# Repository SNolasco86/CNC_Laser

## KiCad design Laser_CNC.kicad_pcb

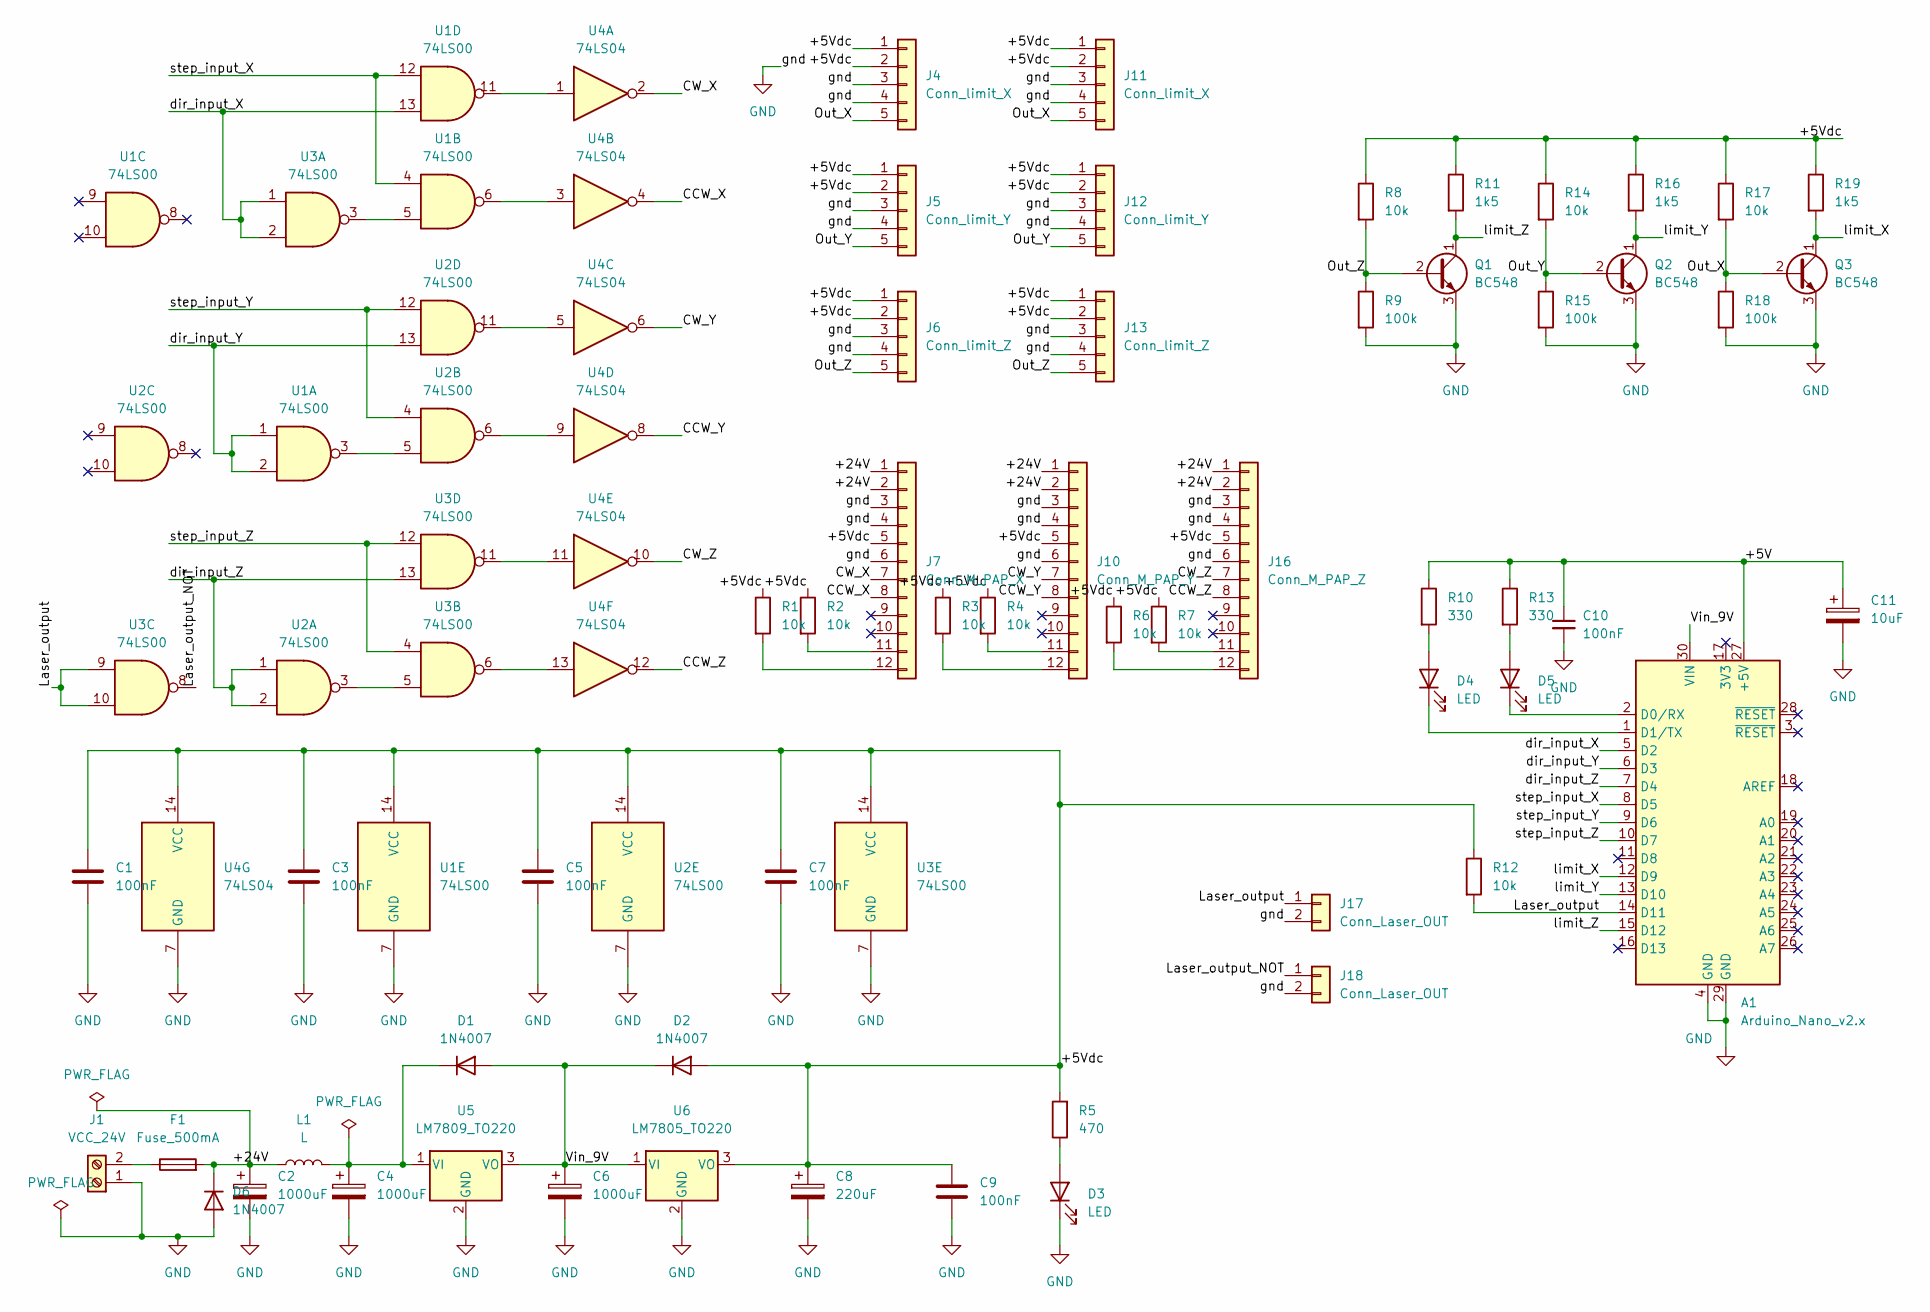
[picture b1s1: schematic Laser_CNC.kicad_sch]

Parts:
A1: Arduino_Nano_v2.x; Arduino_Nano
C1, C3, C5, C7, C9, C10: 100nF; C_Disc_D4.7mm_W2.5mm_P5.00mm
C2: 1000uF; CP_Radial_D13.0mm_P7.50mm
C4, C6: 1000uF; CP_Radial_D13.0mm_P5.00mm
C8: 220uF; CP_Radial_D10.0mm_P3.50mm
C11: 10uF; CP_Radial_D10.0mm_P3.50mm
D1, D2, D6: 1N4007; D_DO-41_SOD81_P10.16mm_Horizontal
D3, D4, D5: LED; LED_D5.0mm
F1: Fuse_500mA; Fuseholder_Cylinder-5x20mm_Stelvio-Kontek_PTF78_Horizontal_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
J1: VCC_24V; TerminalBlock_bornier-2_P5.08mm
J4, J11: Conn_limit_X; Molex_SL_171971-0005_1x05_P2.54mm_Vertical
J5, J12: Conn_limit_Y; Molex_SL_171971-0005_1x05_P2.54mm_Vertical
J6, J13: Conn_limit_Z; Molex_SL_171971-0005_1x05_P2.54mm_Vertical
J7: Conn_M_PAP_X; Molex_SL_171971-0012_1x12_P2.54mm_Vertical
J10: Conn_M_PAP_Y; Molex_SL_171971-0012_1x12_P2.54mm_Vertical
J16: Conn_M_PAP_Z; Molex_SL_171971-0012_1x12_P2.54mm_Vertical
J17, J18: Conn_Laser_OUT; JST_EH_B2B-EH-A_1x02_P2.50mm_Vertical
L1: L; L_Radial_D6.0mm_P4.00mm
Q1, Q2, Q3: BC548; TO-92_Inline
R1, R2, R3, R4, R6, R7, R8, R12, R14, R17: 10k; R_Axial_DIN0207_L6.3mm_D2.5mm_P10.16mm_Horizontal
R5: 470; R_Axial_DIN0207_L6.3mm_D2.5mm_P10.16mm_Horizontal
R9, R15, R18: 100k; R_Axial_DIN0207_L6.3mm_D2.5mm_P10.16mm_Horizontal
R10, R13: 330; R_Axial_DIN0207_L6.3mm_D2.5mm_P10.16mm_Horizontal
R11, R16, R19: 1k5; R_Axial_DIN0207_L6.3mm_D2.5mm_P10.16mm_Horizontal
U1, U2, U3: 74LS00; DIP-14_W7.62mm_LongPads
U4: 74LS04; DIP-14_W7.62mm_LongPads
U5: LM7809_TO220; TO-220-3_Vertical
U6: LM7805_TO220; TO-220-3_Vertical

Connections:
/+5V: A1.27 (+5V), C10.1, C11.1, R10.1, R13.1
/+5Vdc: C1.1, C3.1, C5.1, C7.1, C8.1, C9.1, D2.2 (A), J4.1, J4.2, J5.1, J5.2, J6.1, J6.2, J7.5, J10.5, J11.1, J11.2, J12.1, J12.2, J13.1, J13.2, J16.5, R1.1, R2.1, R3.1, R4.1, R5.2, R6.1, R7.1, R8.1, R11.1, R12.1, R14.1, R16.1, R17.1, R19.1, U1.14 (VCC), U2.14 (VCC), U3.14 (VCC), U4.14 (VCC), U6.3 (VO)
/+24V: C2.1, D6.1 (K), F1.2, J7.1, J7.2, J10.1, J10.2, J16.1, J16.2, L1.1
/CCW_X: J7.8, U4.4
/CCW_Y: J10.8, U4.8
/CCW_Z: J16.8, U4.12
/CW_X: J7.7, U4.2
/CW_Y: J10.7, U4.6
/CW_Z: J16.7, U4.10
/Laser_output: A1.14 (D11), J17.1, R12.2, U3.9, U3.10
/Laser_output_NOT: J18.1, U3.8
/Out_X: J4.5, J11.5, Q3.2 (B), R17.2, R18.1
/Out_Y: J5.5, J12.5, Q2.2 (B), R14.2, R15.1
/Out_Z: J6.5, J13.5, Q1.2 (B), R8.2, R9.1
/Vin_9V: A1.30 (VIN), C6.1, D1.2 (A), D2.1 (K), U5.3 (VO), U6.1 (VI)
/dir_input_X: A1.5 (D2), U1.13, U3.1, U3.2
/dir_input_Y: A1.6 (D3), U1.1, U1.2, U2.13
/dir_input_Z: A1.7 (D4), U2.1, U2.2, U3.13
/limit_X: A1.12 (D9), Q3.1 (C), R19.2
/limit_Y: A1.13 (D10), Q2.1 (C), R16.2
/limit_Z: A1.15 (D12), Q1.1 (C), R11.2
/step_input_X: A1.8 (D5), U1.4, U1.12
/step_input_Y: A1.9 (D6), U2.4, U2.12
/step_input_Z: A1.10 (D7), U3.4, U3.12
GND: A1.4 (GND), A1.29 (GND), C1.2, C2.2, C3.2, C4.2, C5.2, C6.2, C7.2, C8.2, C9.2, C10.2, C11.2, D3.1 (K), D6.2 (A), J1.1, J4.3, J4.4, J5.3, J5.4, J6.3, J6.4, J7.3, J7.4, J7.6, J10.3, J10.4, J10.6, J11.3, J11.4, J12.3, J12.4, J13.3, J13.4, J16.3, J16.4, J16.6, J17.2, J18.2, Q1.3 (E), Q2.3 (E), Q3.3 (E), R9.2, R15.2, R18.2, U1.7 (GND), U2.7 (GND), U3.7 (GND), U4.7 (GND), U5.2 (GND), U6.2 (GND)
unnamed: A1.1 (D1/TX), D4.1 (K)
unnamed: A1.2 (D0/RX), D5.1 (K)
unnamed: C4.1, D1.1 (K), L1.2, U5.1 (VI)
unnamed: D3.2 (A), R5.1
unnamed: D4.2 (A), R10.2
unnamed: D5.2 (A), R13.2
unnamed: F1.1, J1.2
unnamed: J7.11, R2.2
unnamed: J7.12, R1.2
unnamed: J10.11, R4.2
unnamed: J10.12, R3.2
unnamed: J16.11, R7.2
unnamed: J16.12, R6.2
unnamed: U1.3, U2.5
unnamed: U1.5, U3.3
unnamed: U1.6, U4.3
unnamed: U1.11, U4.1
unnamed: U2.3, U3.5
unnamed: U2.6, U4.9
unnamed: U2.11, U4.5
unnamed: U3.6, U4.13
unnamed: U3.11, U4.11

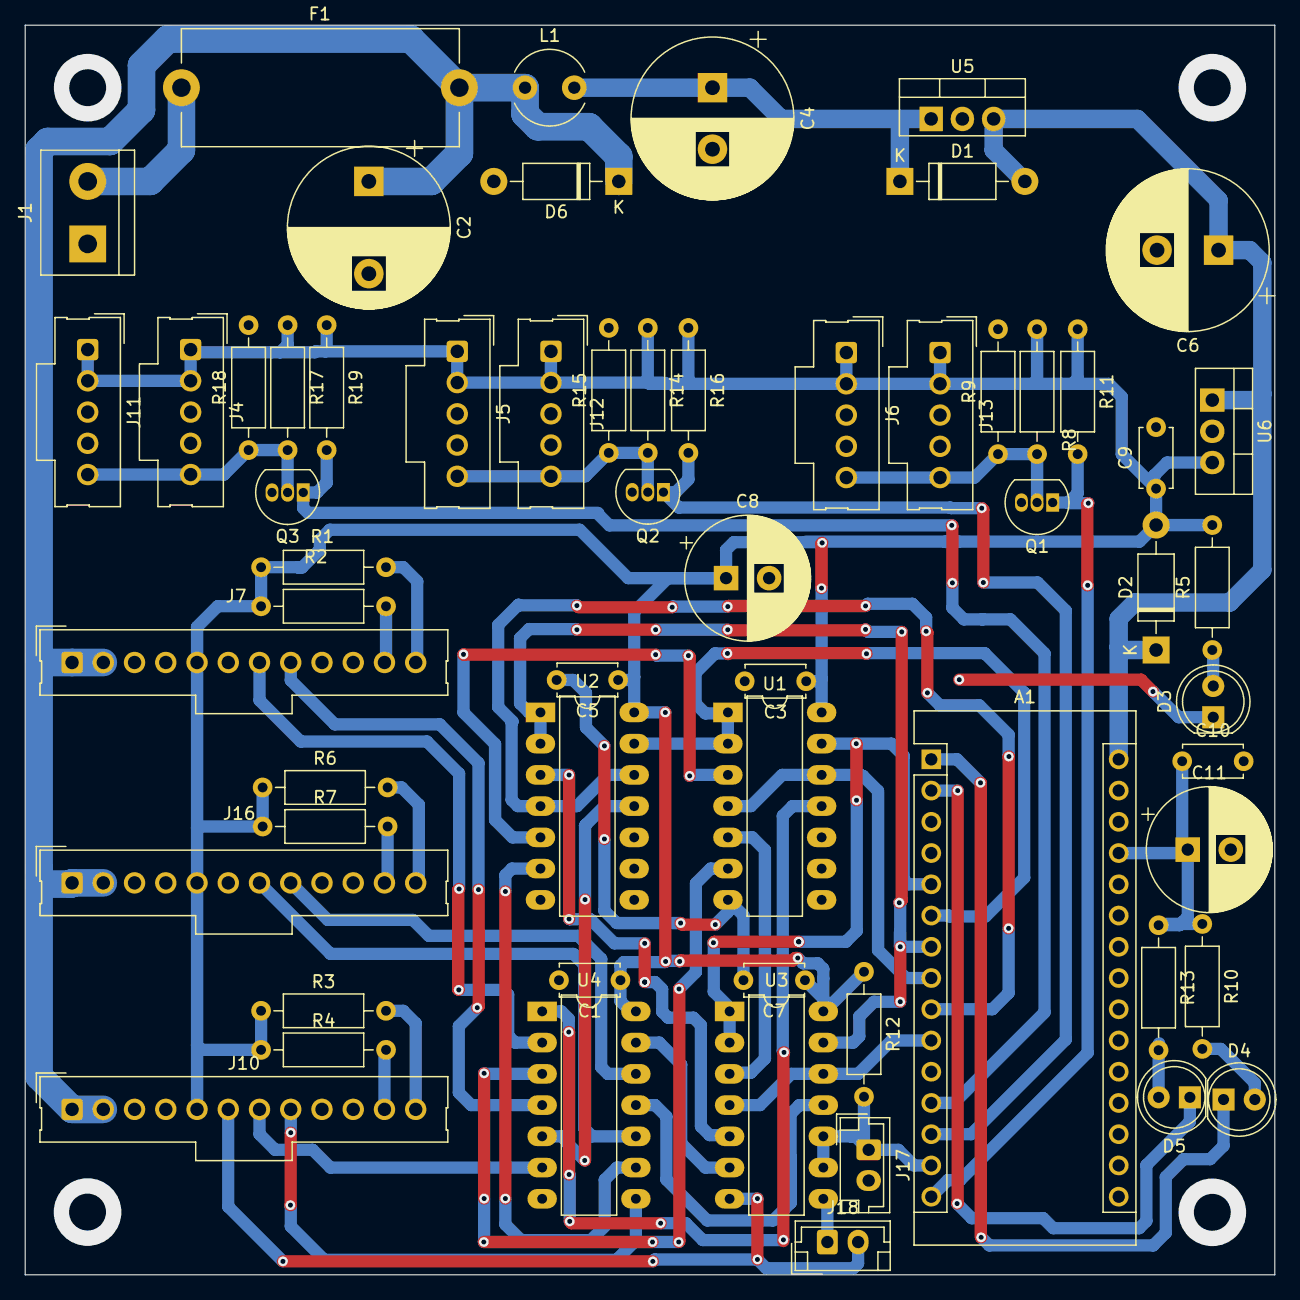
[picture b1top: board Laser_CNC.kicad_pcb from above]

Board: 2 copper layers, 101.6 x 101.6 mm, 60 parts (0 on the bottom side), 47 nets.

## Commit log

2022-08-01 subo atchivo .sch del plaqueta laser
2022-08-10 actualizacion
2022-08-22 PCB listo
